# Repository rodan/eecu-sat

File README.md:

## eecu-sat (Engine ECU signal acquisition tool)

set of multiple modules that allow all analog signals generated and received by a vehicle's Engine Electronic Control Unit to be captured and analyzed. it can either be used as a testing jig for EECUs or as a low level diagnostic tool in which a known good set of signals can be used as reference.

a number of filters and buffers are used to protect the ADCs from transient spikes generated by all inductive loads

```
 source:       https://github.com/rodan/eecu-sat
 author:       Petre Rodan <2b4eda@subdimension.ro>
 license:      GNU GPLv3

 software architecture based on libsigrok and sigrok-cli
 source:       https://sigrok.org
 author:       Bert Vermeulen
 license:      GNU GPLv3
```

more images of the prototype in action are available [here](https://photos.app.goo.gl/Gay5FS8gsCTZkYcH9)

## Project components

project directory structure

 * ./hardware/buffy - kicad based schematics and pcbs for the analog buffer stage
 * ./hardware/pb\_jst-zro*  - kicad based schematics and pcbs for the proxy boards that intercept all EECU signals for a KTM 1090 EECU that uses JST ZRO 36 and 48 pin connectors
 * ./ltspice - spice simulation of the analog buffer schematic
 * ./software/eecu-sat - program that processes the raw analog data exported by [Saleae's Logic](https://www.saleae.com/pages/downloads) and converts them into [sigrok](https://sigrok.org/wiki/File_format:Sigrok/v2) files
 * .doc/ktm\_1090\_wiring.ods - ktm 1090 ECU pinout based on wire harness specs present in the service manual

## eecu-sat software

The software's code is shaped around the [sigrok](https://sigrok.org) library which is a great open-source signal analysis suite. I would have preferred to simply patch libsigrok and sigrok-cli to support the functionality that was needed for this project, however things did not go that smoothly. AFAICT libsigrok assumes that all input signals formats are interlaced, which makes sense from an acquisition system standpoint - samples are usually read by a single thread by switching channels in a loop. so CH1\_sample, CH2\_sample ... CH16\_sample, CH1\_sample, CH2\_sample ... in a row. Also it only supports single-file inputs. Quoting a libsigrok source file,

```
Saleae Logic applications typically export one file per channel. The sigrok
input modules exclusively handle an individual file, existing applications
may not be prepared to handle a set of files, or handle "special" file types
like directories. Some of them will even actively reject such input specs.
Merging multiple exported channels into either another input file or a sigrok
session is supposed to be done outside of this input module.
```

This is the reason why the code is basically a fork of sigrok-cli that contains my own input, output and transform modules that treat all samples in a non-interlaced manner.

### Build requirements

#### Linux
Notable dependencies would be a gcc, make, libzip and the libsigrok headers.

```
cd ./software/eecu-sat
make
```

#### FreeBSD

this is 'Work in progress', not functional just yet. dependencies: gcc13, gmake, gsed

```
export CC='/usr/local/bin/gcc13'
cd ./software/eecu-sat
gmake
```

### Usage

a manual is provided
```
man ./doc/eecu-sat.1
```

***SYNOPSIS***

eecu-sat [-hv] [-i, --input FILENAME_MATCH ] [-o, --output FILE\_PREFIX] [-O, --output-format OUTPUT ] [-t, --triggers TRIGGERS ] [-T, --transform-module TRANSFORM ] [-L, --list]

### TODO list (In Progress)

- [ ] analyze all 48 channels and automatically detect faults based on a known good reference capture
- [x] synchronize multiple sets of 16 channel acquisitions into one 48 channel srzip file
- [x] crop intervals in a signal, based on a trigger definition
- [x] convert Logic exported raw analog signals into srzip files that can be loaded in pulseview
- [x] relabeling capability of channels when seen in pulseview
- [x] 3-point calibration of all analog channels
  - [x] use ini file to input calibration paramenters
  - [x] analyze analog calibration signals, detect the calibration points
  - [x] apply acceptance criteria to input calibration signal
  - [x] export slopes and offsets into calibration ini file

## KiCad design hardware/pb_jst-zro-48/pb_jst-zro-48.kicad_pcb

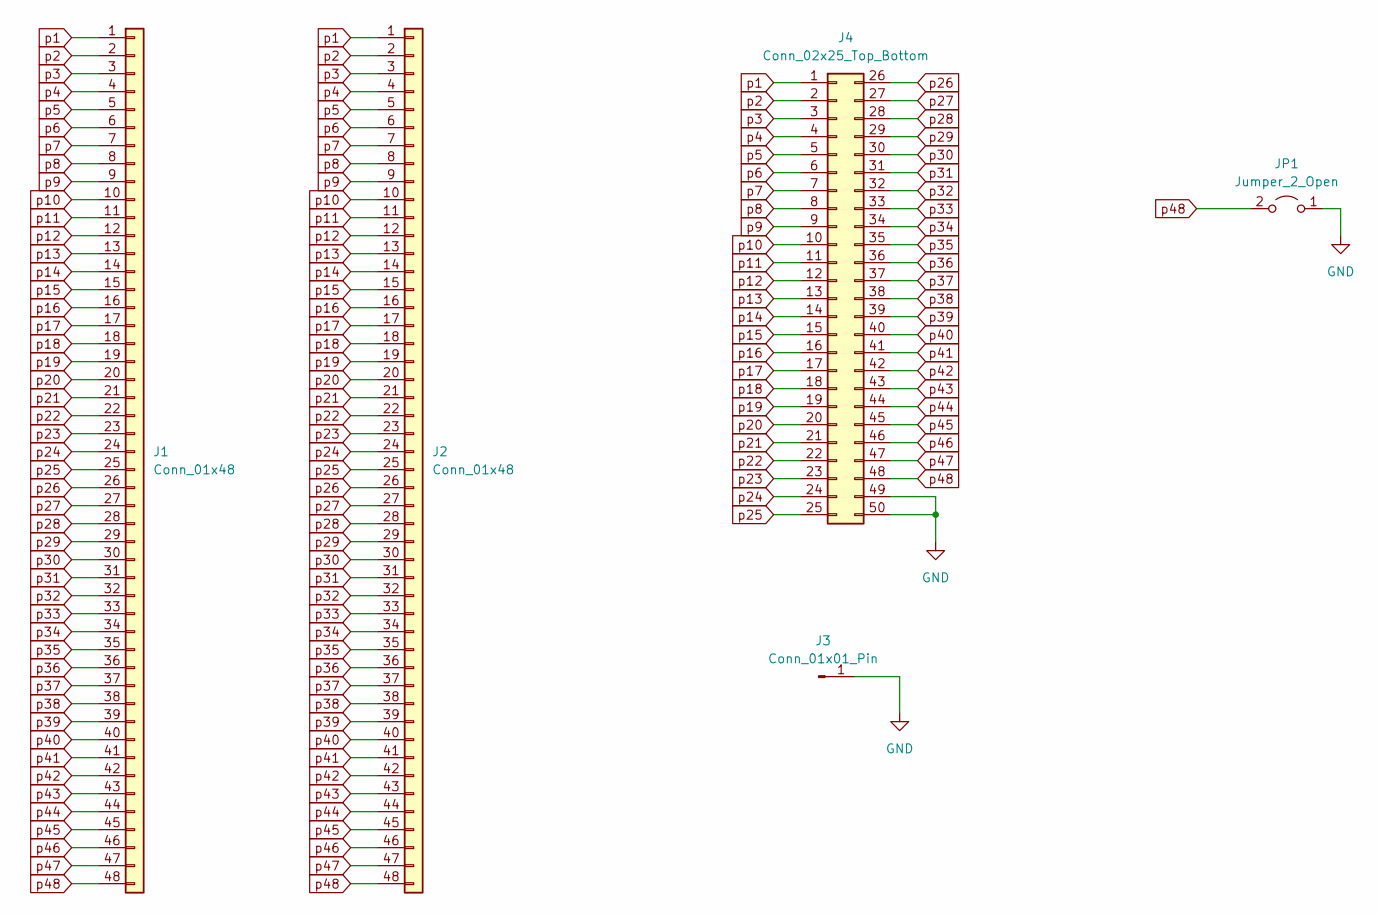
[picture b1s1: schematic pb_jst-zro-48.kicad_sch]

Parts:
J1, J2: Conn_01x48; S48B-ZROK-2A
J3: Conn_01x01_Pin; PinHeader_1x01_P2.54mm_Horizontal
J4: Conn_02x25_Top_Bottom; PinHeader_2x25_P2.54mm_Horizontal
JP1: Jumper_2_Open; PinHeader_1x02_P2.54mm_Vertical

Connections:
GND: J3.1, J4.49, J4.50, JP1.1 (A)
p1: J1.1, J2.1, J4.1
p2: J1.2, J2.2, J4.2
p3: J1.3, J2.3, J4.3
p4: J1.4, J2.4, J4.4
p5: J1.5, J2.5, J4.5
p6: J1.6, J2.6, J4.6
p7: J1.7, J2.7, J4.7
p8: J1.8, J2.8, J4.8
p9: J1.9, J2.9, J4.9
p10: J1.10, J2.10, J4.10
p11: J1.11, J2.11, J4.11
p12: J1.12, J2.12, J4.12
p13: J1.13, J2.13, J4.13
p14: J1.14, J2.14, J4.14
p15: J1.15, J2.15, J4.15
p16: J1.16, J2.16, J4.16
p17: J1.17, J2.17, J4.17
p18: J1.18, J2.18, J4.18
p19: J1.19, J2.19, J4.19
p20: J1.20, J2.20, J4.20
p21: J1.21, J2.21, J4.21
p22: J1.22, J2.22, J4.22
p23: J1.23, J2.23, J4.23
p24: J1.24, J2.24, J4.24
p25: J1.25, J2.25, J4.25
p26: J1.26, J2.26, J4.26
p27: J1.27, J2.27, J4.27
p28: J1.28, J2.28, J4.28
p29: J1.29, J2.29, J4.29
p30: J1.30, J2.30, J4.30
p31: J1.31, J2.31, J4.31
p32: J1.32, J2.32, J4.32
p33: J1.33, J2.33, J4.33
p34: J1.34, J2.34, J4.34
p35: J1.35, J2.35, J4.35
p36: J1.36, J2.36, J4.36
p37: J1.37, J2.37, J4.37
p38: J1.38, J2.38, J4.38
p39: J1.39, J2.39, J4.39
p40: J1.40, J2.40, J4.40
p41: J1.41, J2.41, J4.41
p42: J1.42, J2.42, J4.42
p43: J1.43, J2.43, J4.43
p44: J1.44, J2.44, J4.44
p45: J1.45, J2.45, J4.45
p46: J1.46, J2.46, J4.46
p47: J1.47, J2.47, J4.47
p48: J1.48, J2.48, J4.48, JP1.2 (B)

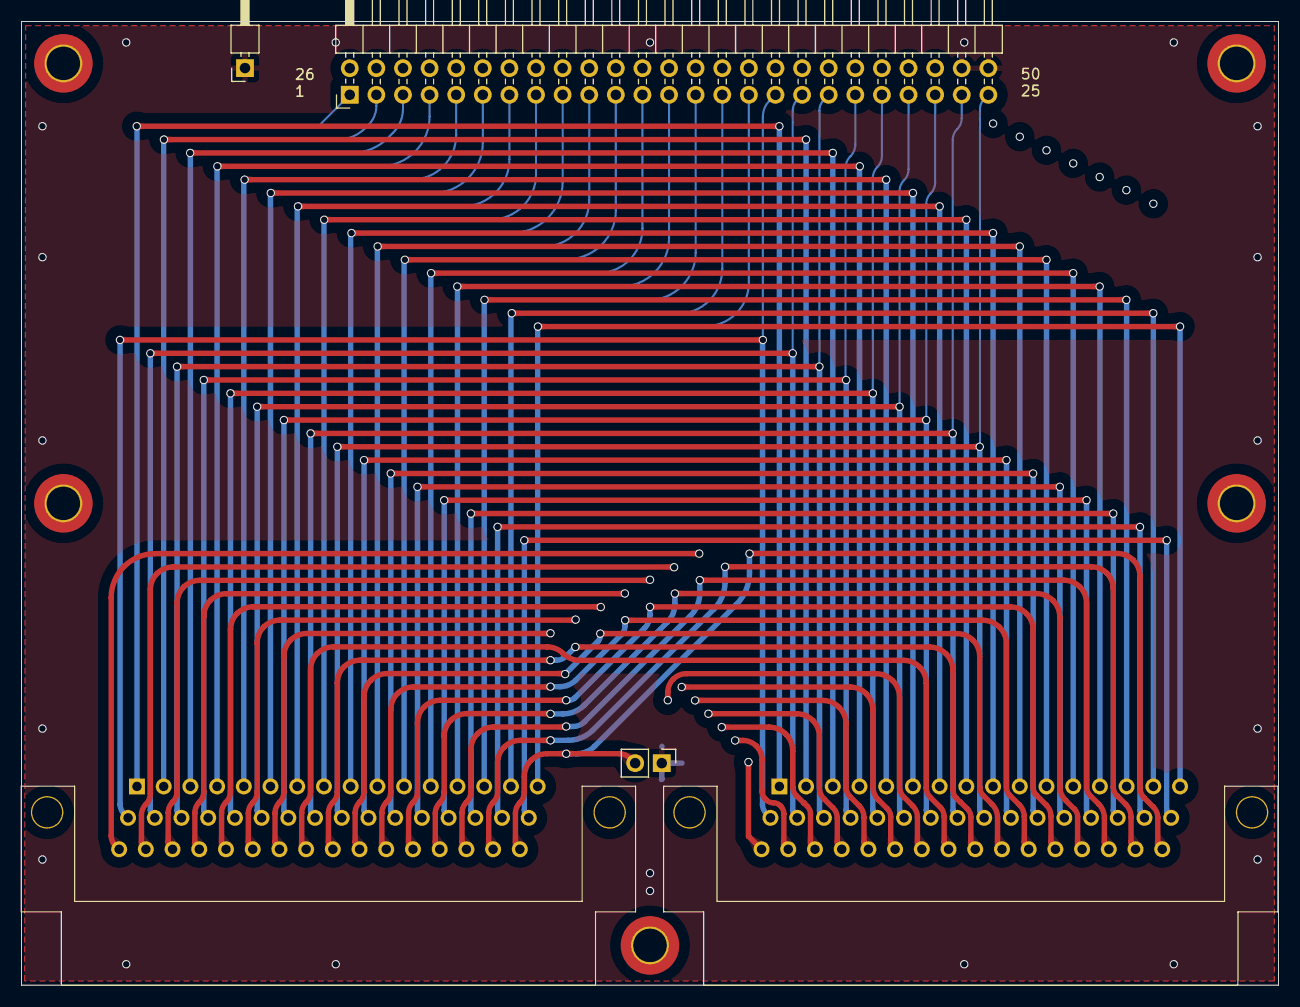
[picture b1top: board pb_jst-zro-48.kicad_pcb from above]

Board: 4 copper layers, 120.0 x 92.0 mm, 5 parts (0 on the bottom side), 49 nets.

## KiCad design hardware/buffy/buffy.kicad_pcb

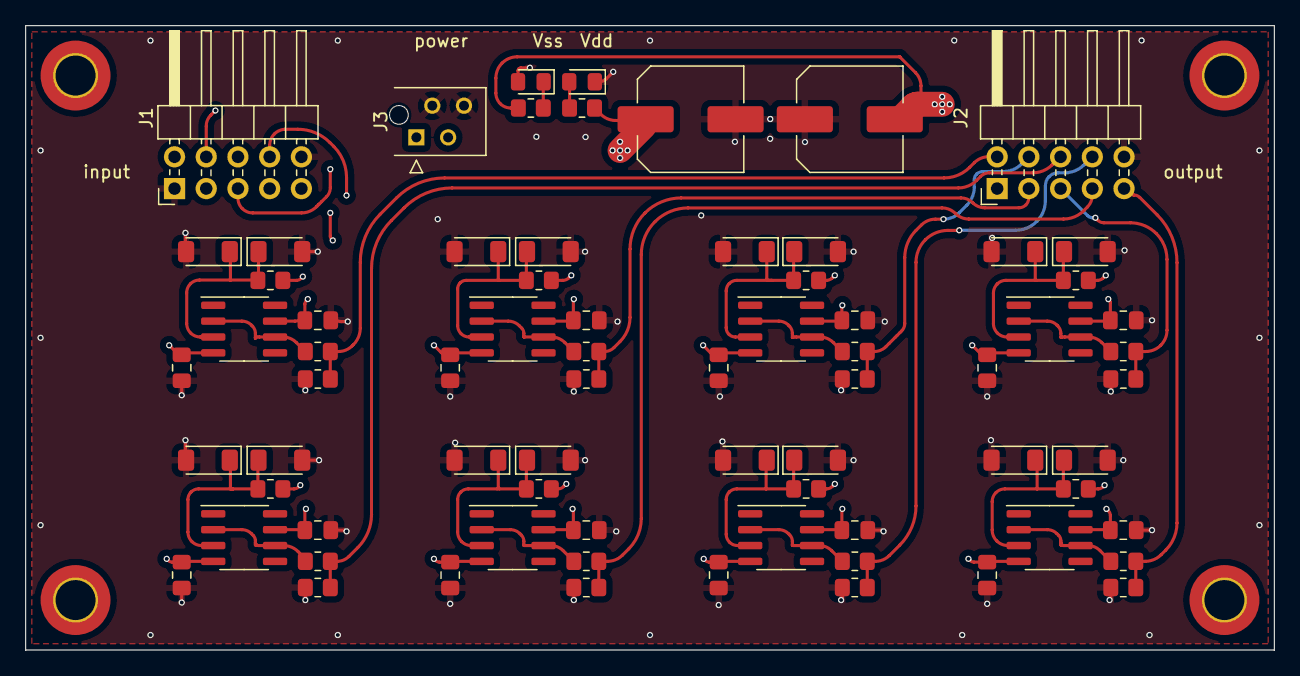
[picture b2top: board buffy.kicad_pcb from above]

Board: 4 copper layers, 100.0 x 50.0 mm, 73 parts (0 on the bottom side), 37 nets.

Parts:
C1, C2: 220u; C_Elec_8x10.2
C102, C103, C112, C113, C122, C123, C132, C133, C142, C143, C152, C153, C162, C163, C172, C173: 100n; C_0805_2012Metric_Pad1.18x1.45mm_HandSolder
D1, D2: LED; LED_0805_2012Metric_Pad1.15x1.40mm_HandSolder
D101, D111, D121, D131, D141, D151, D161, D171: TZMB15-GS08; D_MiniMELF
D102, D112, D122, D132, D142, D152, D162, D172: BZV55B15; D_MiniMELF
J1, J2: Conn_02x05_Odd_Even; PinHeader_2x05_P2.54mm_Horizontal
J3: Conn_01x04_Pin; TE_Micro-MaTch_215079-4_2x02_P1.27mm_Vertical
R1, R2: 100k; R_0805_2012Metric_Pad1.20x1.40mm_HandSolder
R101, R111, R121, R131, R141, R151, R161, R171: 10K; R_0805_2012Metric_Pad1.20x1.40mm_HandSolder
R105, R115, R125, R135, R145, R155, R165, R175: 5K 0.1%; R_0805_2012Metric_Pad1.20x1.40mm_HandSolder
R106, R116, R126, R136, R146, R156, R166, R176: 10K 0.1%; R_0805_2012Metric_Pad1.20x1.40mm_HandSolder
U101, U111, U121, U131, U141, U151, U161, U171: OPA140; SOIC-8_3.9x4.9mm_P1.27mm

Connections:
GND: C1.2, C2.1, C102.2, C103.1, C112.2, C113.1, C122.2, C123.1, C132.2, C133.1, C142.2, C143.1, C152.2, C153.1, C162.2, C163.1, C172.2, C173.1, D1.1 (K), D2.2 (A), D101.2 (A), D102.2 (A), D111.2 (A), D112.2 (A), D121.2 (A), D122.2 (A), D131.2 (A), D132.2 (A), D141.2 (A), D142.2 (A), D151.2 (A), D152.2 (A), D161.2 (A), D162.2 (A), D171.2 (A), D172.2 (A), J1.1, J1.10, J2.1, J2.10, J3.2, J3.4, R106.2, R116.2, R126.2, R136.2, R146.2, R156.2, R166.2, R176.2
unnamed: D1.2 (A), R1.2
unnamed: D2.1 (K), R2.2
unnamed: D101.1 (K), D102.1 (K), R101.1, U101.3 (+)
unnamed: D111.1 (K), D112.1 (K), R111.1, U111.3 (+)
unnamed: D121.1 (K), D122.1 (K), R121.1, U121.3 (+)
unnamed: D131.1 (K), D132.1 (K), R131.1, U131.3 (+)
unnamed: D141.1 (K), D142.1 (K), R141.1, U141.3 (+)
unnamed: D151.1 (K), D152.1 (K), R151.1, U151.3 (+)
unnamed: D161.1 (K), D162.1 (K), R161.1, U161.3 (+)
unnamed: D171.1 (K), D172.1 (K), R171.1, U171.3 (+)
unnamed: R105.1, U101.2 (-), U101.6
unnamed: R115.1, U111.2 (-), U111.6
unnamed: R125.1, U121.2 (-), U121.6
unnamed: R135.1, U131.2 (-), U131.6
unnamed: R145.1, U141.2 (-), U141.6
unnamed: R155.1, U151.2 (-), U151.6
unnamed: R165.1, U161.2 (-), U161.6
unnamed: R175.1, U171.2 (-), U171.6
VDD: C1.1, C102.1, C112.1, C122.1, C132.1, C142.1, C152.1, C162.1, C172.1, J3.1, R1.1, U101.7 (V+), U111.7 (V+), U121.7 (V+), U131.7 (V+), U141.7 (V+), U151.7 (V+), U161.7 (V+), U171.7 (V+)
VSS: C2.2, C103.2, C113.2, C123.2, C133.2, C143.2, C153.2, C163.2, C173.2, J3.3, R2.1, U101.4 (V-), U111.4 (V-), U121.4 (V-), U131.4 (V-), U141.4 (V-), U151.4 (V-), U161.4 (V-), U171.4 (V-)
in0: J1.2, R101.2
in1: J1.3, R111.2
in2: J1.4, R121.2
in3: J1.5, R131.2
in4: J1.6, R141.2
in5: J1.7, R151.2
in6: J1.8, R161.2
in7: J1.9, R171.2
out0: J2.2, R105.2, R106.1
out1: J2.3, R115.2, R116.1
out2: J2.4, R125.2, R126.1
out3: J2.5, R135.2, R136.1
out4: J2.6, R145.2, R146.1
out5: J2.7, R155.2, R156.1
out6: J2.8, R165.2, R166.1
out7: J2.9, R175.2, R176.1

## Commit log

2024-08-17 initial import
2024-08-17 esat -> eecu-sat
2024-08-18 start scanning project with coverity
2024-08-19 add inih git submodule
2024-08-19 add calib.h, restructure README todo list
2024-08-20 switch to using linked list library from the contiki-ng project
2024-08-21 parse calibration parameter file
2024-08-21 split action functions out of main
2024-08-21 fix fd resource leak in case lseek fails
2024-08-22 calib init working
2024-08-25 calib: read per-channel ini data
2024-08-25 add test scripts
2024-08-25 add generic output interface based on libsigrok's implementation
2024-08-25 selectable output format
2024-08-26 add transform modules
2024-08-26 testing calibration
2024-08-27 add output module options
2024-08-27 move session fcts out of main.c
2024-08-27 cleanup
2024-08-27 perform initcal as an output module
2024-08-27 fix possible pointer dereference
2024-08-27 use sdi->channels instead of a global variable, use sdi->priv to store current channel and chunk info
2024-08-27 fix coverity defects
2024-08-28 output_analog: add channel offset
2024-09-01 change license to GPLv3 due to libsigrok
2024-09-01 align source with libsigrok and also link against it
2024-09-01 move some struct to sigrok_internal header
2024-09-01 add copyright headers
2024-09-01 add unit tests
2024-09-01 add sample signals used by unit tests
2024-09-02 use libsigrok-style error levels
2024-09-03 add parsing of trigger option
2024-09-03 triggers are triggering
2024-09-07 signal crop based on trigger is working
2024-09-08 add saleae header into ch_data_t
2024-09-08 output_srzip: create metadata from scratch if not provided, calculate samplerate based on input headers
2024-09-09 unit_testing: update metadata inside sample_files archive
2024-09-09 unit_testing: add output_srzip_metadata_import test
2024-09-09 add some FreeBSD compatibility changes
2024-09-10 output_analog: add header to output files
2024-09-10 cleanup, valid output generated
2024-09-11 readme todo list updated
2024-09-11 cleanup doc
2024-09-11 add manual
2024-09-11 add markdown version of manual
2024-09-12 use g_malloc0 instead of calloc, add valgrind make target
2024-09-12 use err_msg for all error reporting
2024-10-14 freebsd port, part 1
2024-10-14 main.c: sort input filenames in the channels GSList using a natural sort algo
2024-10-14 fix run_session / prepare id order
